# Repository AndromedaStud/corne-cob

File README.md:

# Corne Cob 🌽
*A modern Ergogen redesign of the popular Corne layout.*

---

## Project Status
**Version:** v0.9  

> This version is still in development and may not be ready for production.

---

## Overview
**Corne Cob** builds on the [Corne](https://github.com/foostan/crkbd) layout and extends [Narkoleptika’s josukey](https://github.com/Narkoleptika/josukey) using [Ergogen](https://ergogen.xyz/).  
Designed with improved ergonomics, better hardware support, and a few quality-of-life enhancements.

---

## Key Features and Additions
Compared to **josukey** and similar corne layouts, Corne Cob includes:

- OLED display
- Larger battery for extended wireless life
- Angled case for improved typing comfort (not in v1.0)
- Separate left and right PCBs for easier assembly
- 1.5u thumb key support for more keycap options
- 6-column design (versus the standard 5-column Corne)
- Horizontal reset key for easier access
- North facing RGB for better choc keycap support

---
## Case
*Designed with Onshape based on left PCB*

See the document [here](https://cad.onshape.com/documents/4b27800fb1d5766ea9f563d0/w/4f20d77dd6337f2d27187dd8/e/7361c0148c8c6276b82e26d4?renderMode=0&uiState=6aea463c3d68943d1f0ed62a)  *(For .stl download, look at releases)*

---
## Built With
- [Ergogen](https://ergogen.xyz/) — PCB base design 
- [KiCad](https://kicad.org/) — Schematic and layout editing  
- [josukey](https://github.com/Narkoleptika/josukey) — Base layout inspiration
- [OnShape](https://Onshape.com/) — Case design

---

## Roadmap
- [X] Finalize v1 PCB layout
- [X] Setup price sheet for budget
- [ ] Test case fit and alignment  
- [ ] Validate power delivery and charging circuit  
- [ ] Release build guide and firmware configuration

---
## Parts List
Price estimate chart found [here](https://docs.google.com/spreadsheets/d/1HdLqQ5FFB6K92mRF0pi76wc0cOreWh93cLWDCBQdG54/edit?usp=sharing) <--

- Nice!Nano v2 2 [Microcontroller](https://typeractive.xyz/products/nice-nano)
- SSD1306 I2C IIC OLED 2 
- 1800 mah battery 2 (considering [PS3 Controller batteries](https://www.amazon.com/Replacement-Playstation-Controller-CECHZC2E-CECHZC2U-3/dp/B09726K2LC))
- Power Switch >2 [PCM12SMTR](https://www.digikey.com/en/products/detail/c-k/PCM12SMTR/1640112)
- Reset Switch >2 [EVQ-PUC02K](https://www.digikey.com/en/products/detail/panasonic-electronic-components/EVQ-PUC02K/286336)
- RGB LED >42 [S35353RGBSK6812MINID001](https://www.digikey.com/en/products/detail/home-run-tech/S35353RGBSK6812MINID001/25879535)
- Diode >42 [1N4148W](https://www.digikey.com/en/products/detail/smc-diode-solutions/1N4148W/6022450)
- Battery Adapter [S2B-PH-K-S](https://www.digikey.com/en/products/detail/jst-sales-america-inc/S2B-PH-K-S/926626)
- Choc v1 switches >42 [Pro Red](https://typeractive.xyz/products/choc-switches?variant=46024772387047)
- Choc v1 keycaps >42 
- Rubber Feet >8 [SJ5382](https://www.digikey.com/en/products/detail/3m/SJ5382/3866079)
- M2 screws >10
---

## Acknowledgements
Special thanks to **Narkoleptika** for the original [josukey](https://github.com/Narkoleptika/josukey) project, and to the **Ergogen** and **Corne** communities for their open-source contributions.

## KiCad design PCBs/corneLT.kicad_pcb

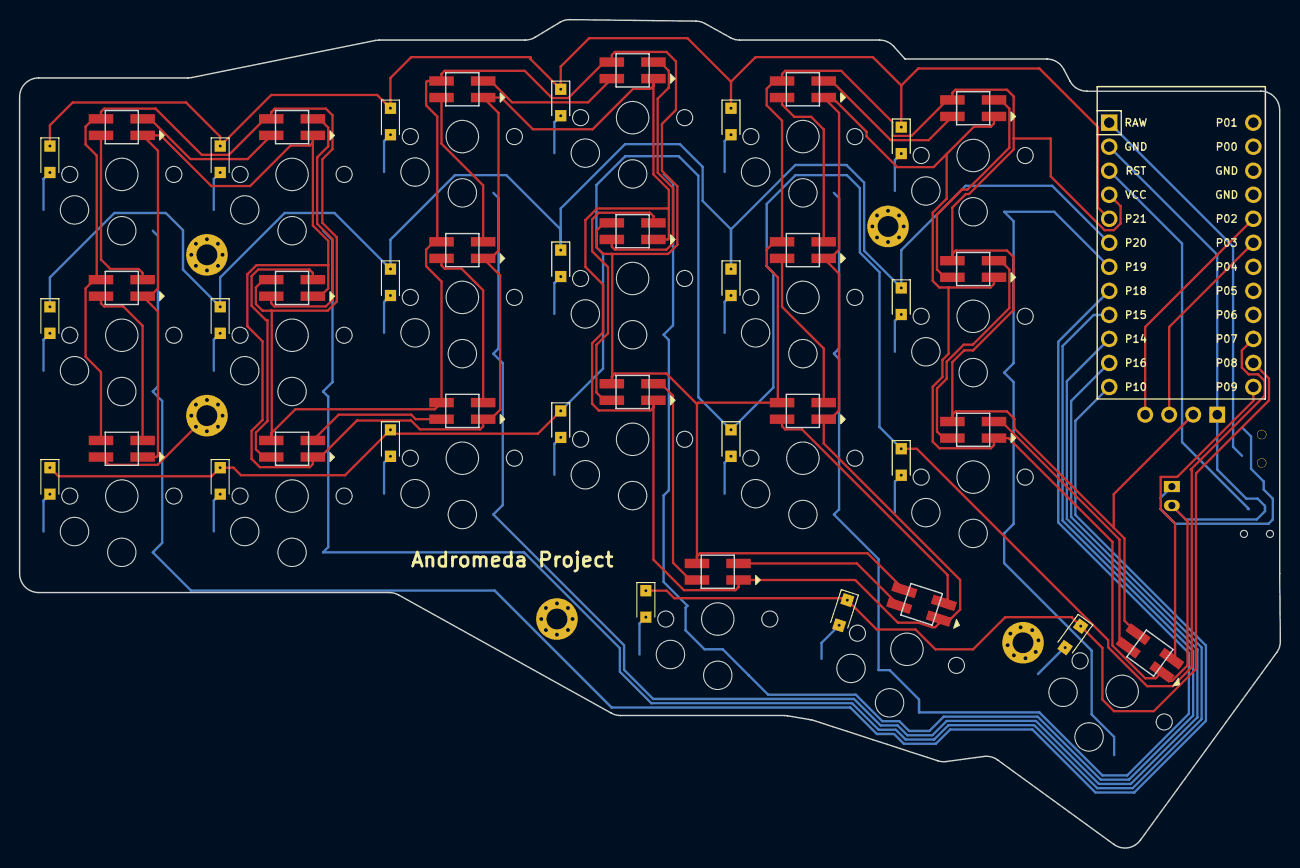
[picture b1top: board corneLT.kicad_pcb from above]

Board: 2 copper layers, 133.3 x 87.6 mm, 73 parts (0 on the bottom side), 59 nets.

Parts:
B1: Panasonic_EVQPUL_EVQPUC
D1, D2, D3, D4, D5, D6, D7, D8, D9, D10, D11, D12, D13, D14, D15, D16, D17, D18, D19, D20, D21: Nexperia_CFP3_SOD-123W
JST1: JST_PH_S2B-PH-K_02x2.00mm_Angled
LED1, LED2, LED3, LED4, LED5, LED6, LED7, LED8, LED9, LED10, LED11, LED12, LED13, LED14, LED15, LED16, LED17, LED18, LED19, LED20, LED21: WS2812B
MCU1: ProMicro
OLED1: OLED; OLED_headers
S1, S2, S3, S4, S5, S6, S7, S8, S9, S10, S11, S12, S13, S14, S15, S16, S17, S18, S19, S20, S21: PG1350
T1: SPDT_C128955
_1, _2, _3, _4, _5: MountingHole_2.2mm_M2_Pad_Via

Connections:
GND: B1.1, JST1.2, LED1.3, LED2.3, LED3.3, LED4.3, LED5.3, LED6.3, LED7.3, LED8.3, LED9.3, LED10.3, LED11.3, LED12.3, LED13.3, LED14.3, LED15.3, LED16.3, LED17.3, LED18.3, LED19.3, LED20.3, LED21.3, MCU1.2, MCU1.15, MCU1.16, OLED1.1
P2: MCU1.17, OLED1.4
P3: MCU1.18, OLED1.3
P7: D1.1, D4.1, D7.1, D10.1, D13.1, D16.1, MCU1.22
P8: D19.1, D20.1, D21.1, MCU1.23
P9: LED21.4, MCU1.24
P10: MCU1.12, S1.1, S2.1, S3.1
P14: MCU1.10, S7.1, S8.1, S9.1
P15: MCU1.9, S10.1, S11.1, S12.1, S19.1
P16: MCU1.11, S4.1, S5.1, S6.1
P18: MCU1.8, S13.1, S14.1, S15.1, S20.1
P19: MCU1.7, S16.1, S17.1, S18.1, S21.1
P20: D2.1, D5.1, D8.1, D11.1, D14.1, D17.1, MCU1.6
P21: D3.1, D6.1, D9.1, D12.1, D15.1, D18.1, MCU1.5
RAW: MCU1.1, T1.2
RST: B1.2, MCU1.3
VCC: LED1.1, LED2.1, LED3.1, LED4.1, LED5.1, LED6.1, LED7.1, LED8.1, LED9.1, LED10.1, LED11.1, LED12.1, LED13.1, LED14.1, LED15.1, LED16.1, LED17.1, LED18.1, LED19.1, LED20.1, LED21.1, MCU1.4, OLED1.2
main_index_bottom: D13.2, S13.2
main_index_home: D14.2, S14.2
main_index_top: D15.2, S15.2
main_inner_bottom: D16.2, S16.2
main_inner_home: D17.2, S17.2
main_inner_top: D18.2, S18.2
main_middle_bottom: D10.2, S10.2
main_middle_home: D11.2, S11.2
main_middle_top: D12.2, S12.2
main_pinky2_bottom: D4.2, S4.2
main_pinky2_home: D5.2, S5.2
main_pinky2_top: D6.2, S6.2
main_pinky_bottom: D1.2, S1.2
main_pinky_home: D2.2, S2.2
main_pinky_top: D3.2, S3.2
main_ring_bottom: D7.2, S7.2
main_ring_home: D8.2, S8.2
main_ring_top: D9.2, S9.2
pos: JST1.1, T1.1
rgb_main_index_bottom: LED13.4, LED14.2
rgb_main_index_home: LED14.4, LED15.2
rgb_main_index_top: LED15.4, LED18.2
rgb_main_inner_bottom: LED16.4, LED21.2
rgb_main_inner_home: LED16.2, LED17.4
rgb_main_inner_top: LED17.2, LED18.4
rgb_main_middle_bottom: LED10.4, LED19.2
rgb_main_middle_home: LED10.2, LED11.4
rgb_main_middle_top: LED11.2, LED12.4
rgb_main_pinky2_bottom: LED4.4, LED7.2
rgb_main_pinky2_home: LED4.2, LED5.4
rgb_main_pinky2_top: LED5.2, LED6.4
rgb_main_pinky_bottom: LED1.4, LED2.2
rgb_main_pinky_home: LED2.4, LED3.2
rgb_main_pinky_top: LED3.4, LED6.2
rgb_main_ring_bottom: LED7.4, LED8.2
rgb_main_ring_home: LED8.4, LED9.2
rgb_main_ring_top: LED9.4, LED12.2
rgb_thumb_home_home: LED13.2, LED20.4
rgb_thumb_inner_home: LED19.4, LED20.2
thumb_home_home: D20.2, S20.2
thumb_inner_home: D19.2, S19.2
thumb_outer_home: D21.2, S21.2

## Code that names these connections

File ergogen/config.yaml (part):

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                            led_in: "rgb_{{name}}"
                        home:
                            led_in: "rgb_{{name}}"
                            led_out: rgb_main_pinky_bottom
                        top:
                            led_in: "rgb_{{name}}"
                            led_out: rgb_main_pinky_home
                pinky2:
                    key:
                        col_net: P16
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                    rows:
                        bottom:
                            led_in: "rgb_{{name}}"
                            led_out: rgb_main_pinky2_home
                        home:
                            led_in: "rgb_{{name}}"
                            led_out: rgb_main_pinky2_top
                        top:
                            led_in: "rgb_{{name}}"
                            led_out: rgb_main_pinky_top
                ring:
                    key:
                        col_net: P14
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                    rows:
                        bottom:
                            led_in: "rgb_{{name}}"
                            led_out: rgb_main_pinky2_bottom
                        home:
                            led_in: "rgb_{{name}}"
                            led_out: rgb_main_ring_bottom
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                -   ref: thumb_inner_home
                    shift: [-0.6cx, -0.6cy]

                -   ref: main_pinky_bottom
                    shift: [1.6cx, -0.6cy]
                -   ref: main_pinky_bottom
                    shift: [0.6cx, -0.6cy]
                -   ref: main_pinky_bottom
                    shift: [-0.6cx, -0.6cy]

                -   ref: main_pinky_top
                    shift: [-0.6cx, 0.6cy]
                -   ref: main_pinky_top
                    shift: [0.4cx, 0.6cy]

                -   ref: main_ring_top
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                -   ref: thumb_inner_home
                    shift: [-0.6cx, -0.6cy - 2]

                -   ref: main_pinky_bottom
                    shift: [1.6cx, -0.6cy - 2]
                -   ref: main_pinky_bottom
                    shift: [0.6cx, -0.6cy - 2]
                -   ref: main_pinky_bottom
                    shift: [-0.6cx - 2, -0.6cy - 2]

                -   ref: main_pinky_top
                    shift: [-0.6cx - 2, 0.6cy + 2]
                -   ref: main_pinky_top
                    shift: [0.4cx, 0.6cy + 2]

                -   ref: main_ring_top
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        -   what: circle
            radius: screwHead
            where:
                ref: main_pinky_home
                shift: [9, 8.5]
        -   what: circle
            radius: screwHead
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        -   what: circle
            radius: screwHead
            where:
                ref: main_pinky_bottom
                shift: [9, 8.5]
        -   what: circle
            radius: screwHead
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        -   what: circle
            radius: screwShaft
            where:
                ref: main_pinky_home
                shift: [9, 8.5]
        -   what: circle
            radius: screwShaft
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        -   what: circle
            radius: screwShaft
            where:
                ref: main_pinky_bottom
                shift: [9, 8.5]
        -   what: circle
            radius: screwShaft
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            mountinghole2:
                what: mountinghole
                where:
                    ref: main_pinky_home
                    shift: [9, 8.5]
            mountinghole3:
                what: mountinghole
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            mountinghole4:
                what: mountinghole
                where:
                    ref: main_pinky_bottom
                    shift: [9, 8.5]
            mountinghole5:
                what: mountinghole
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
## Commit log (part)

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2025-10-24 Update README.md
    update README
2025-10-24 Added Ergogen file
2025-10-24 v0.1
2025-10-24 v0.2
2025-10-27 v0.3
2025-11-03 v0.8
2025-11-17 v0.9
    Ergogen files have been updated to final version but PCB has not been finalized.
2026-05-25 Fixed a variety of PCB issues and finalized layout
2026-05-25 v0.9
    PCB fixed and board design finalized, ready for test build
2026-05-25 v9.1
    PCB finished and L/R schematics fixed
2026-05-25 v9.1
    test PCBs finished
